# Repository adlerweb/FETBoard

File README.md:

# FETBoard

FETBoard is a Shield that connects to either an NodeMCU or Arduino Pro Mini. It breaks out 7 Inputs and 5 Outputs. Two inputs can be changed into outputs via jumpers. Inputs use a resistor to provide some level of protection. Outputs use a SI2302DS which is rated at 2.4A. Due to the losses involved I would suggest to stay below 1A per channel. On the Pro Mini Pins used for SPI where kept clear to allow for interfacing additional modules.

## Warnings

The board was a quick'n'dirty solution to get some of my connections done. It was created somewhere around 2am, so there is a lot of stuff that could be done better.

* There are no Pull-Ups/Down for either In- or Output. Especially outputs might not behave as expected if your code doesn't drive the outputs or the controller crashes
* Wiring is a mess, don't even try to find any logic here

## Things required

* NodeMCU or Arduino Pro Mini (duh!)
* Enough female pin headers to accommodate the controller mentioned. Use the spring loaded type, turned ones won't fit the controllers pins.
* Any 5.08mm Screw Terminals
* 7 x SI2302DS
* 7 x Resistor for SI2302DS - something between 500Ω and 5kΩ should be OK. Lower values lead to less losses when using PWM, higher ones don't stress the controller as much.
* 7 x Resistor for inputs - Anything you're comfortable with. Some 10s of kΩ should be a good compromise

## Pinout

| Side   | Pin | NodeMCU | Pro Mini |
|--------|-----|---------|----------|
| Input  | 1 (Left)   | GND     | GND      |
| Input  | 2   | D6 (JP1)| D7 (JP1) |
| Input  | 3   | D5 (JP2)| D4 (JP2) |
| Input  | 4   | N/C     | A3       |
| Input  | 5   | 3       | A2       |
| Input  | 6   | D8      | A1       |
| Input  | 7   | D7      | A0       |
| Output | 8   | D0      | D2       |
| Output | 1 (Left)  | Vin     | RAW      |
| Output | 2   | D6 (JP1)| D7 (JP1) |
| Output | 3   | D5 (JP2)| D4 (JP2) |
| Output | 4   | N/C     | D9       |
| Output | 5   | D4      | D8       |
| Output | 6   | D3      | D6       |
| Output | 7   | D2      | D5       |
| Output | 8   | D1      | D3       |

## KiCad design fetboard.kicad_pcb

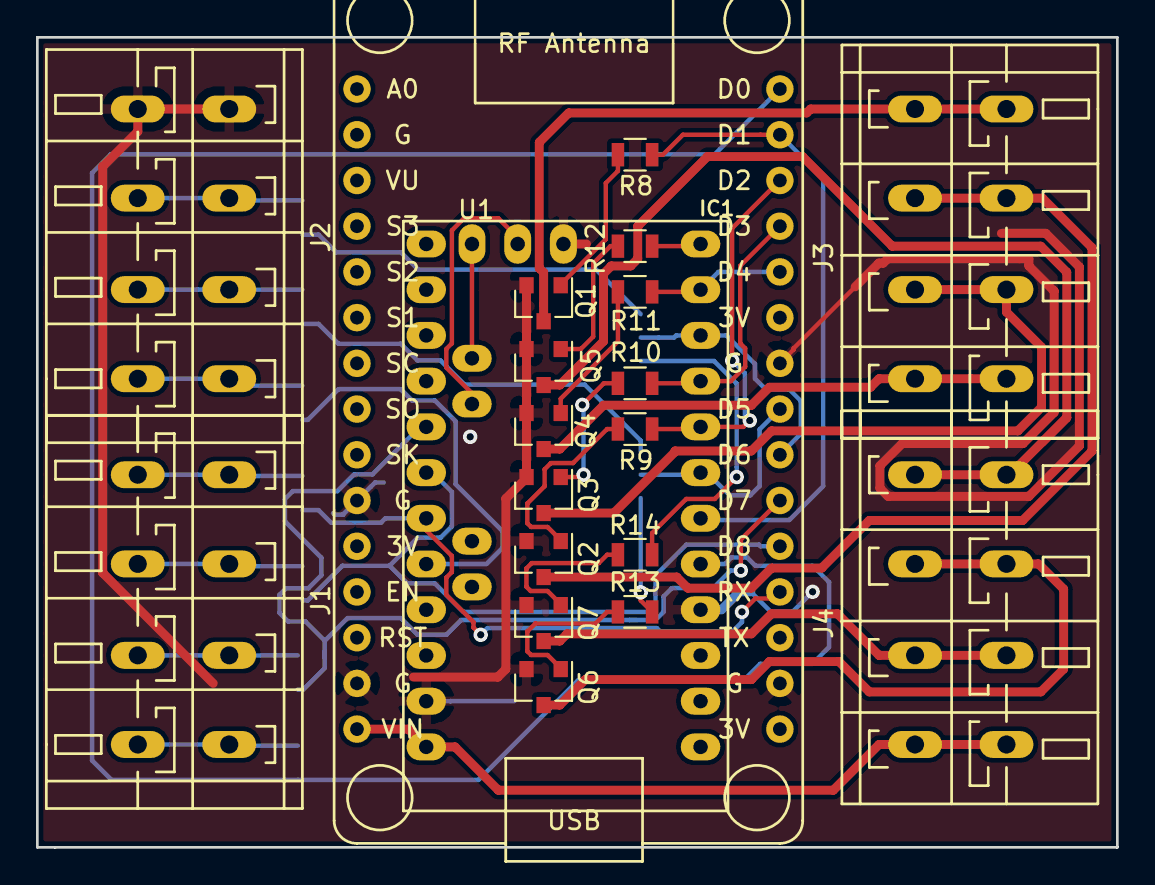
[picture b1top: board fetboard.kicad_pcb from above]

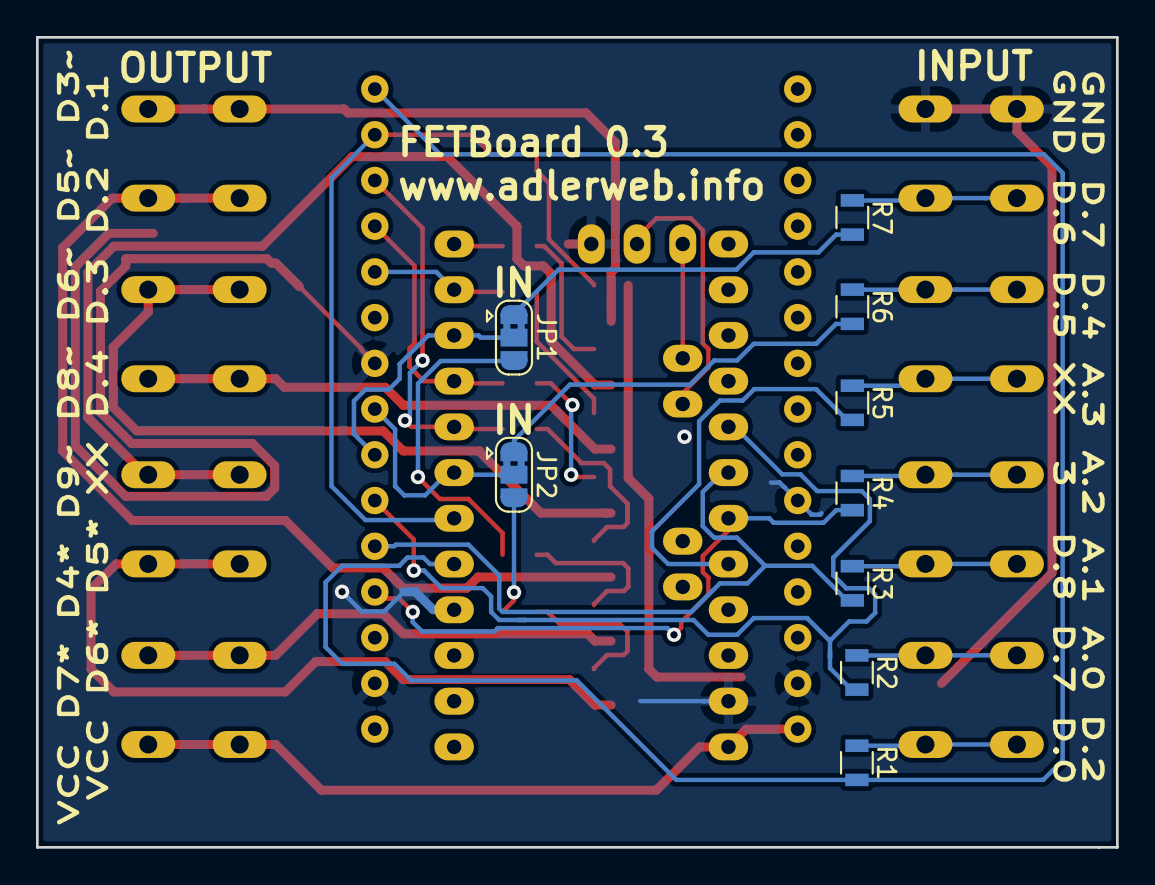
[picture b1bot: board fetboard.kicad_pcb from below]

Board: 2 copper layers, 60.0 x 45.0 mm, 29 parts (9 on the bottom side), 39 nets.

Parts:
IC1: ArduinoProMini; pro_mini
J1: IN1; TerminalBlock_WAGO-236_2Stift_RM5mm_4pol
J2: IN2; TerminalBlock_WAGO-236_2Stift_RM5mm_4pol
J3: OUT1; TerminalBlock_WAGO-236_2Stift_RM5mm_4pol
J4: OUT2; TerminalBlock_WAGO-236_2Stift_RM5mm_4pol
JP1, JP2: 3xJ; SolderJumper-3_P1.3mm_Bridged2Bar12_RoundedPad1.0x1.5mm
Q1, Q2, Q3, Q4, Q5, Q6, Q7: SI2302; SOT-23
R1, R2, R3, R4, R5, R6, R7, R8, R9, R10, R11, R12, R13, R14: 2.2kΩ; R_0805
U1: NodeMCU1.0(ESP-12E); ESP12F-Devkit-V3

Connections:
/IO0: IC1.7, JP2.2, U1.23
/IO1: IC1.10, JP1.2, U1.22
/In0: IC1.5, R1.2, U1.30
/In1: IC1.17, R2.2, U1.21
/In2: IC1.18, R3.2, U1.20
/In3: IC1.19, R4.2, U1.19
/In4: IC1.20, R5.2
/In5: JP2.1, R6.2
/In6: JP1.1, R7.2
/Out0: IC1.6, R8.2, U1.29
/Out1: IC1.8, R9.2, U1.28
/Out2: IC1.9, R10.2, U1.27
/Out3: IC1.11, R11.2, U1.26
/Out4: IC1.12, R12.2
/Out5: JP2.3, R13.2
/Out6: JP1.3, R14.2
GND: IC1.4, IC1.23, IC1.29, J2.4, Q1.2, Q2.2, Q3.2, Q4.2, Q5.2, Q6.2, Q7.2, U1.10, U1.14, U1.17, U1.24
unnamed: J1.1, R1.1
unnamed: J1.2, R2.1
unnamed: J1.3, R3.1
unnamed: J1.4, R4.1
unnamed: J2.1, R5.1
unnamed: J2.2, R6.1
unnamed: J2.3, R7.1
unnamed: J3.1, Q1.3
unnamed: J3.2, Q2.3
unnamed: J3.3, Q3.3
unnamed: J3.4, Q4.3
unnamed: J4.1, Q5.3
unnamed: J4.2, Q6.3
unnamed: J4.3, Q7.3
unnamed: Q1.1, R8.1
unnamed: Q2.1, R9.1
unnamed: Q3.1, R10.1
unnamed: Q4.1, R11.1
unnamed: Q5.1, R12.1
unnamed: Q6.1, R13.1
unnamed: Q7.1, R14.1
VCC: IC1.24, J4.4, U1.15

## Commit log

2019-03-10 Dummy-Import for long lost rev1 sources
2019-03-10 rev3
